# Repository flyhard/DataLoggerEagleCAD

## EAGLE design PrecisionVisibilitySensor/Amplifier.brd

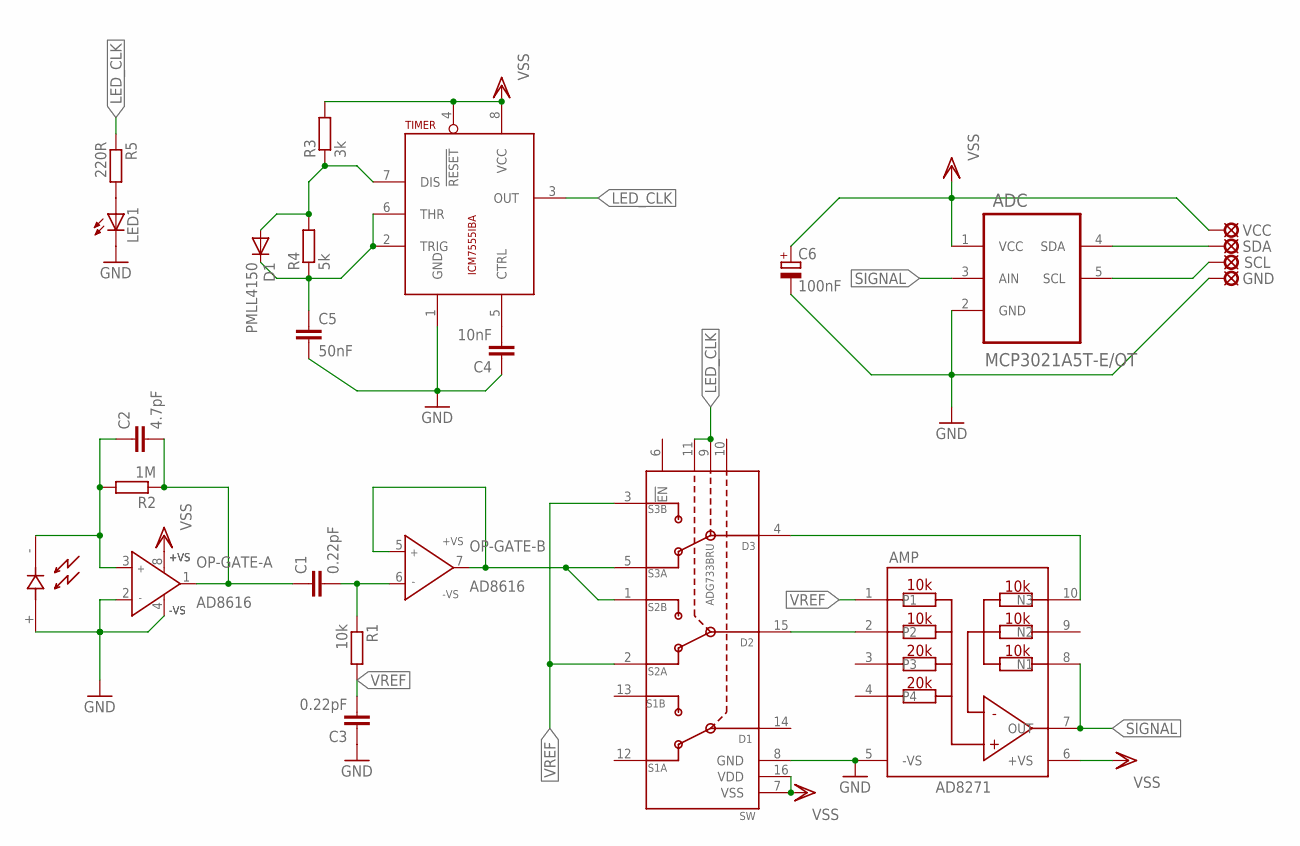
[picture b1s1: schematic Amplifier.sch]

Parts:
ADC: MCP3021A5T-E/OT; SOT95P270X145-5N
AMP: AD8271; MSOP10
C1, C3: 0.22pF; C1206
C2: 4.7pF; C1206
C4: 10nF; C1206
C5: 50nF; C1206
C6: 100nF; SMC_B
D1: PMLL4150; SOD80C
GND: LSP10
LED1: LED5MM
OP-: AD8616; MSOP08
R1: 10k; R1206
R2: 1M; R1206
R3: 3k; R1206
R4: 5k; R1206
R5: 220R; R1206
SCL: LSP10
SDA: LSP10
SW: ADG733BRU; TSSOP16
TIMER: ICM7555IBA; SOIC8
U$1: VBT101BH; TO-46
VCC: LSP10

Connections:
GND: ADC.2 (GND), AMP.5 (-VS), C3.1, C4.1, C5.2, C6.-, GND.MP, LED1.K (C), OP-.2 (IN-), OP-.4 (-VS), SW.8 (GND), TIMER.1 (GND), U$1.+
LED_CLK: SW.9 (A2), SW.11 (A0), TIMER.3 (OUT)
unnamed: OP-.5 (IN+), OP-.7 (OUT), SW.1 (S2B), SW.5 (S3A)
unnamed: AMP.10 (N3), SW.4 (D3)
unnamed: AMP.2, SW.15 (D2)
unnamed: ADC.5 (SCL), SCL.MP
unnamed: C1.2, OP-.6 (IN-), R1.1
unnamed: C1.1, C2.2, OP-.1 (OUT), R2.1
unnamed: C2.1, OP-.3 (IN+), R2.2, U$1.-
unnamed: LED1.A, R5.2
unnamed: C5.1, D1.C, R4.1, TIMER.2 (TRIG), TIMER.6 (THR)
unnamed: D1.A, R3.1, R4.2, TIMER.7 (DIS)
unnamed: ADC.4 (SDA), SDA.MP
unnamed: C4.2, TIMER.5 (CTRL)
SIGNAL: ADC.3 (AIN), AMP.7 (OUT), AMP.8 (N1)
VREF: AMP.1, C3.2, R1.2, SW.2 (S2A), SW.3 (S3B)
VSS: ADC.1 (VCC), AMP.6 (+VS), C6.+, OP-.8 (+VS), R3.2, SW.7 (VSS), SW.16 (VDD), TIMER.4 (!RESET), TIMER.8 (VCC), VCC.MP

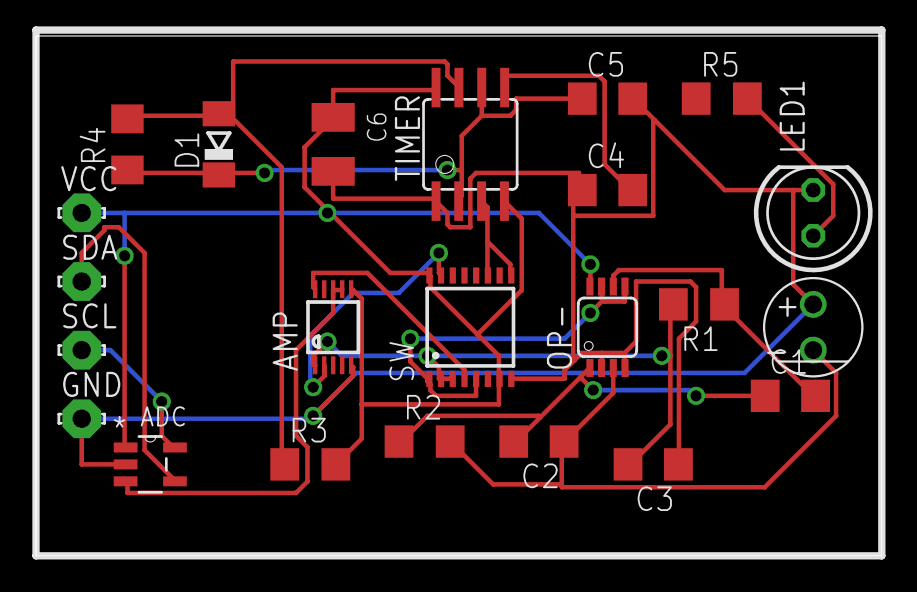
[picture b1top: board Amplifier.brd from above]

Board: 2 copper layers, 47.0 x 28.9 mm, 23 parts (0 on the bottom side), 17 nets.

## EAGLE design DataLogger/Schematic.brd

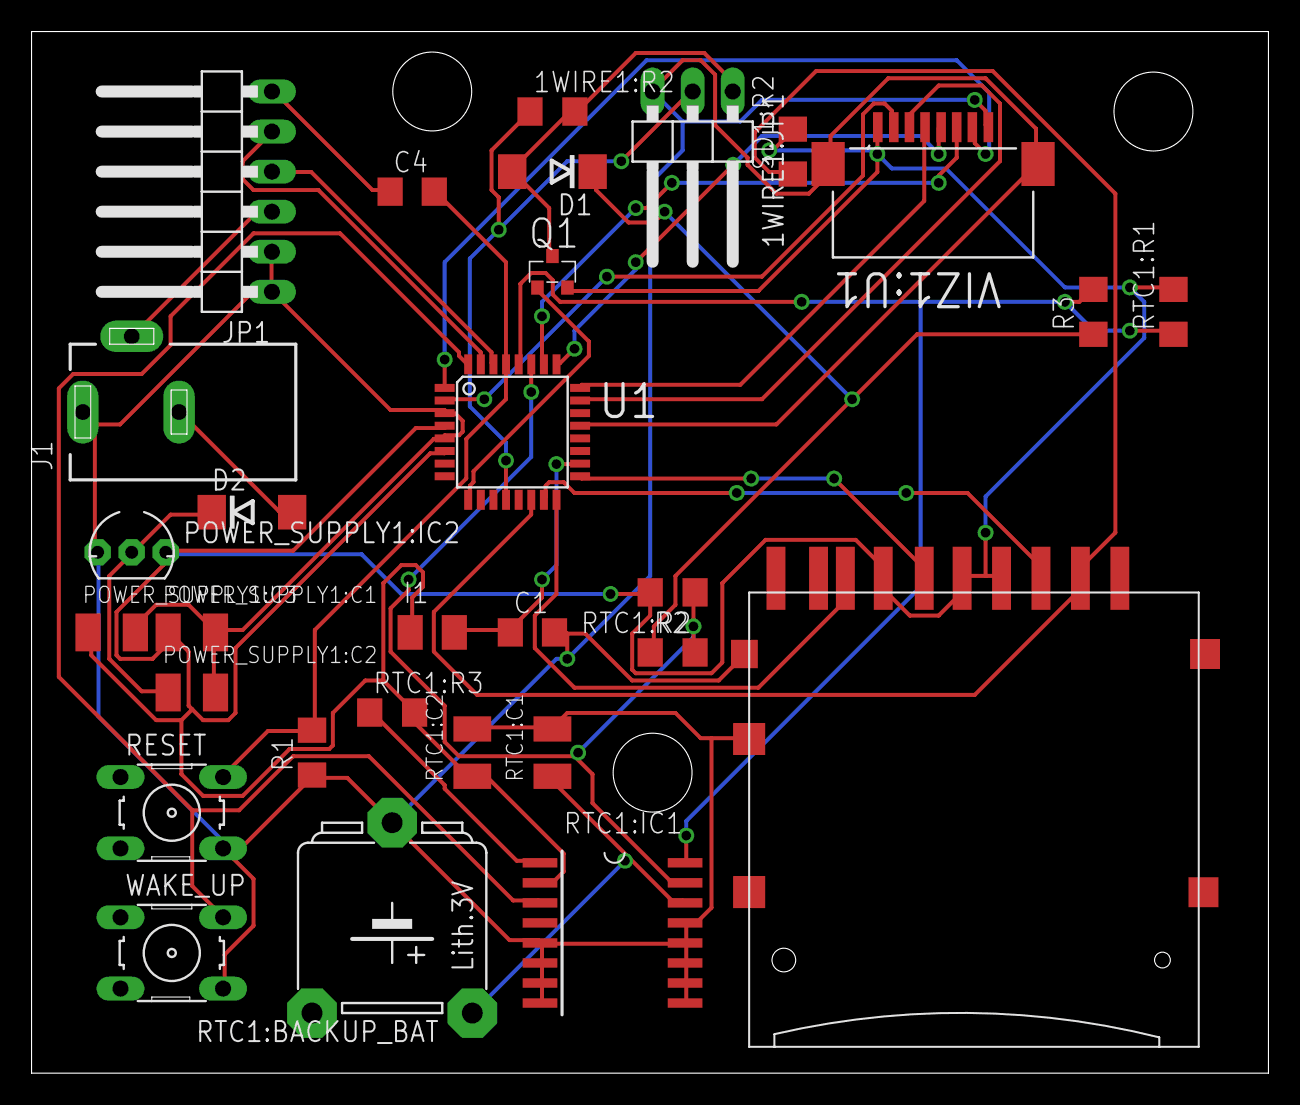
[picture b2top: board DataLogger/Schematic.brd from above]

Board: 2 copper layers, 78.4 x 66.0 mm, 30 parts (0 on the bottom side), 29 nets.

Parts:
1WIRE1:JP1: 1X03/90
1WIRE1:R2: 4,7k; R1206
C1, C4: 100nF; C1206
D1, D2: DO214AA
I1: 10nH; L3225M
J1: DCJ0202
JP1: FTDI friend; 1X06/90
POWER_SUPPLY1:C1: 0.33nF; SMC_B
POWER_SUPPLY1:C2, POWER_SUPPLY1:C3: 100nF; SMC_B
POWER_SUPPLY1:IC2: MCP1700 3302E; TO92-INLINE
Q1: IRLML5203; MICRO3
R1: 1M; R1206
R2, R3: 10k; R1206
RESET: B3F-10XX
RTC1:BACKUP_BAT: CR03N
RTC1:C1, RTC1:C2: 0.1F; SMC_B
RTC1:IC1: DS3231SN; SOIC-16W
RTC1:R1, RTC1:R2, RTC1:R3: 10k; R1206
SD1:R2: 10k; R1206
SD1:U$1: SDMMC18650; SDCARD
U1: ATMEGA328P-AU; TQFP32-08
VIZ1:U1: 52207-0885; MOLEX_52207-0885
WAKE_UP: B3F-10XX

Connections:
A0: U1.23, VIZ1:U1.3
A1: U1.24, VIZ1:U1.4
A2: U1.25, VIZ1:U1.5
A3: U1.26, VIZ1:U1.6
A4: R2.2, RTC1:IC1.15, RTC1:R2.1, U1.27
A5: R3.2, RTC1:IC1.16, RTC1:R1.1, U1.28
AVCC: C1.1, I1.2, U1.18
D2: RTC1:IC1.3, U1.32, WAKE_UP.2
D3: U1.1, VIZ1:U1.7
D4: U1.2, VIZ1:U1.2
D5: Q1.1, U1.9
D8: 1WIRE1:JP1.2, 1WIRE1:R2.1, U1.12
D10: SD1:R2.1, SD1:U$1.1, U1.14
D11: SD1:U$1.2, U1.15
D12: SD1:U$1.7, U1.16
D13: SD1:U$1.5, U1.17
DTR: C4.1, JP1.6
GND: 1WIRE1:JP1.3, C1.2, J1.1, JP1.1, JP1.2, POWER_SUPPLY1:C1.-, POWER_SUPPLY1:C2.-, POWER_SUPPLY1:C3.-, POWER_SUPPLY1:IC2.1, R1.1, RESET.4, RTC1:BACKUP_BAT.-, RTC1:C1.-, RTC1:C2.-, RTC1:IC1.5, RTC1:IC1.6, RTC1:IC1.7, RTC1:IC1.8, RTC1:IC1.9, RTC1:IC1.10, RTC1:IC1.11, RTC1:IC1.12, RTC1:IC1.13, SD1:U$1.COM, SD1:U$1.MT1, U1.3, U1.5, U1.21, VIZ1:U1.8, VIZ1:U1.9, VIZ1:U1.10, WAKE_UP.4
unnamed: D2.A, J1.3
unnamed: D2.C, POWER_SUPPLY1:C2.+, POWER_SUPPLY1:IC2.2
unnamed: D1.C, R2.1, R3.1
RESET: C4.2, R1.2, RESET.2, U1.29
RTC1:32KHZ: RTC1:IC1.1, RTC1:R3.1
RTC1:VBAT: RTC1:BACKUP_BAT.+, RTC1:C1.+, RTC1:IC1.14
RX: JP1.5, U1.31
TX: JP1.4, U1.30
VCC: I1.1, POWER_SUPPLY1:C1.+, POWER_SUPPLY1:C3.+, POWER_SUPPLY1:IC2.3, Q1.2, RTC1:C2.+, RTC1:IC1.2, RTC1:R1.2, RTC1:R2.2, RTC1:R3.2, SD1:R2.2, SD1:U$1.3, SD1:U$1.4, SD1:U$1.6, U1.4, U1.6, VIZ1:U1.1
VCC5V: J1.2, JP1.3
VSS_SWITCHED: 1WIRE1:JP1.1, 1WIRE1:R2.2, D1.A, Q1.3

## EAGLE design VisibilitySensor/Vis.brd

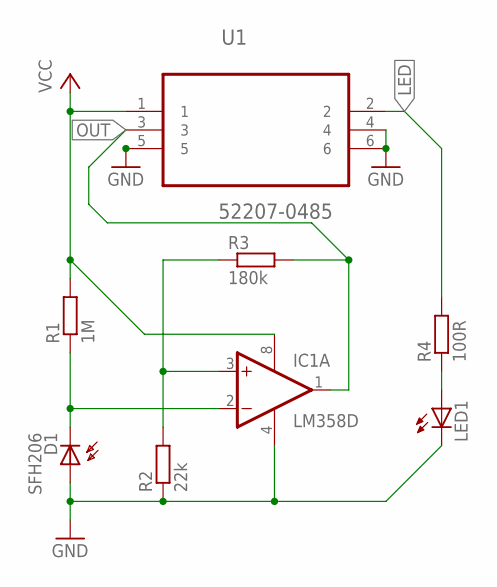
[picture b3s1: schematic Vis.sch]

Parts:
D1: SFH206
IC1: LM358D; SO08; MPN LM358DR
LED1: LED5MM; MPN 151053GS03000
R1: 1M; R1206
R2: 22k; R1206
R3: 180k; R1206; MPN CRGH1206F180K
R4: 100R; R1206
U1: 52207-0485; MOLEX_52207-0485

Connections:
GND: D1.A, IC1.4 (V-), LED1.K (C), R2.1, U1.4, U1.5, U1.6
LED: R4.2, U1.2
unnamed: D1.K (C), IC1.2 (-IN), R1.1
unnamed: LED1.A, R4.1
unnamed: IC1.3 (+IN), R2.2, R3.1
OUT: IC1.1 (OUT), R3.2, U1.3
VCC: IC1.8 (V+), R1.2, U1.1

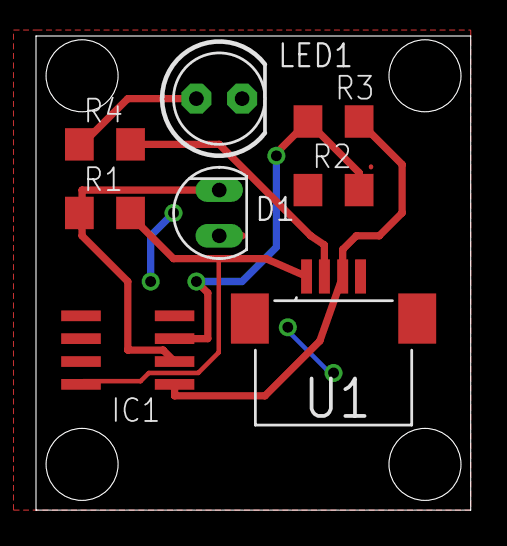
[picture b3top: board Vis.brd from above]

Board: 2 copper layers, 24.2 x 26.3 mm, 8 parts (0 on the bottom side), 7 nets.

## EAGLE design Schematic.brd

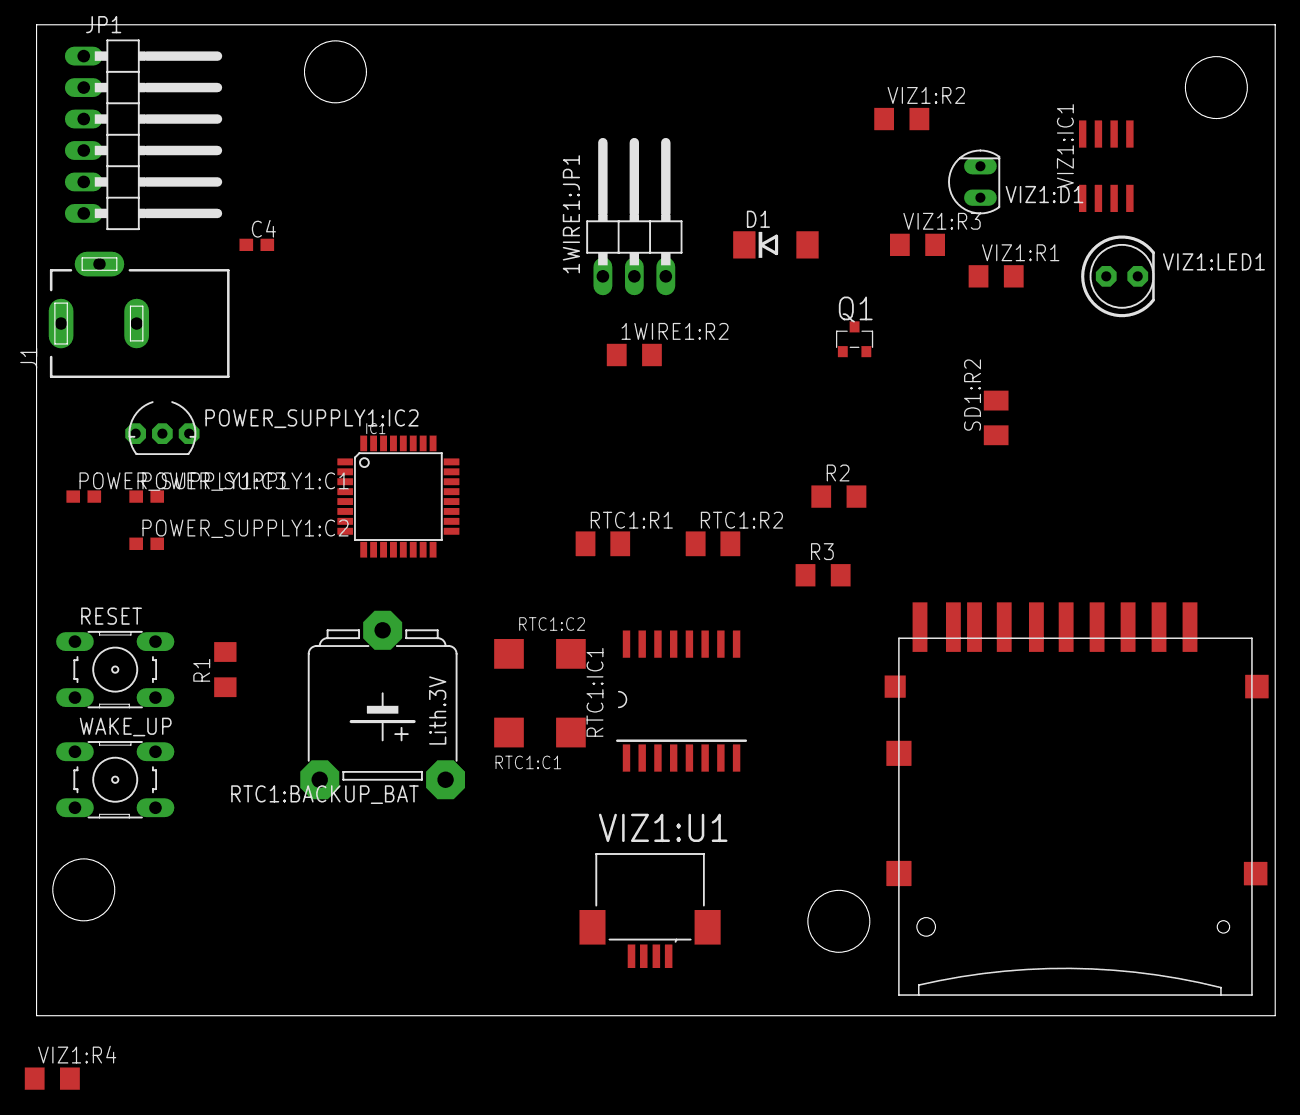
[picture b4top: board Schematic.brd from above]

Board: 2 copper layers, 100.0 x 80.0 mm, 33 parts (0 on the bottom side), 25 nets, no tracks yet.

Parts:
1WIRE1:JP1: 1X03/90
1WIRE1:R2: 4,7k; R1206
C4: 100nF; C1608
D1: DO214AA
IC1: MEGA8-AI; TQFP32-08
J1: DCJ0202
JP1: FTDI friend; 1X06/90
POWER_SUPPLY1:C1: 0.33nF; C1608
POWER_SUPPLY1:C2, POWER_SUPPLY1:C3: 100nF; C1608
POWER_SUPPLY1:IC2: MCP1700 3302E; TO92-INLINE
Q1: IRLML5203; MICRO3
R1: 1M; R1206
R2, R3: 10k; R1206
RESET: B3F-10XX
RTC1:BACKUP_BAT: CR03N
RTC1:C1, RTC1:C2: SMC_C
RTC1:IC1: SOIC-16W
RTC1:R1, RTC1:R2: M1206
SD1:R2: 10k; M1206
SD1:U$1: SDMMC18650; SDCARD
VIZ1:D1: SFH206
VIZ1:IC1: LM358D; SO08
VIZ1:LED1: LED5MM
VIZ1:R1: 1M; R1206
VIZ1:R2: 22k; R1206
VIZ1:R3: 180k; R1206
VIZ1:R4: R1206
VIZ1:U1: 52207-0485; MOLEX_52207-0485
WAKE_UP: B3F-10XX

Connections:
DTR: C4.1, JP1.6
GND: 1WIRE1:JP1.3, IC1.3, IC1.5, J1.1, JP1.1, JP1.2, R1.1, RESET.4, RTC1:BACKUP_BAT.-, RTC1:C1.-, RTC1:C2.-, RTC1:IC1.5, RTC1:IC1.6, RTC1:IC1.7, RTC1:IC1.8, RTC1:IC1.9, RTC1:IC1.10, RTC1:IC1.11, RTC1:IC1.12, RTC1:IC1.13, SD1:U$1.COM, SD1:U$1.MT1, VIZ1:D1.A, VIZ1:IC1.4, VIZ1:LED1.K, VIZ1:R2.1, VIZ1:U1.4, VIZ1:U1.5, VIZ1:U1.6, WAKE_UP.4
unnamed: IC1.9, Q1.1
unnamed: J1.3, POWER_SUPPLY1:C2.1, POWER_SUPPLY1:IC2.2
unnamed: POWER_SUPPLY1:C1.2, POWER_SUPPLY1:C2.2, POWER_SUPPLY1:C3.2, POWER_SUPPLY1:IC2.1
unnamed: IC1.28, R3.2, RTC1:R1.2
unnamed: IC1.27, R2.2, RTC1:R2.2
unnamed: IC1.15, SD1:U$1.2
unnamed: IC1.14, SD1:R2.1, SD1:U$1.1
unnamed: IC1.32, RTC1:IC1.3, WAKE_UP.2
unnamed: 1WIRE1:JP1.2, 1WIRE1:R2.1, IC1.12
unnamed: D1.C, R2.1, R3.1
unnamed: IC1.23, VIZ1:R4.2, VIZ1:U1.2
unnamed: IC1.24, VIZ1:IC1.1, VIZ1:R3.2
RESET: C4.2, IC1.29, R1.2, RESET.2
RTC1:N$1: RTC1:IC1.15, RTC1:R2.1
RTC1:N$2: RTC1:IC1.16, RTC1:R1.1
RTC1:VBAT: RTC1:BACKUP_BAT.+, RTC1:C1.+, RTC1:IC1.14
RX: IC1.31, JP1.5
VCC: POWER_SUPPLY1:C1.1, POWER_SUPPLY1:C3.1, POWER_SUPPLY1:IC2.3, Q1.2, RTC1:C2.+, RTC1:IC1.2, SD1:R2.2, SD1:U$1.3, SD1:U$1.6, VIZ1:IC1.8, VIZ1:R1.2
VCC5V: J1.2, JP1.3
VIZ1:N$1: VIZ1:D1.K, VIZ1:IC1.2, VIZ1:R1.1
VIZ1:N$2: VIZ1:LED1.A, VIZ1:R4.1
VIZ1:N$3: VIZ1:IC1.3, VIZ1:R2.2, VIZ1:R3.1
VSS_SWITCHED: 1WIRE1:JP1.1, 1WIRE1:R2.2, D1.A, Q1.3

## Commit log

2015-08-12 Added
2015-08-12 More components
2015-08-12 More development
2015-08-12 More libs
2015-08-13 Slight changes
2015-08-13 Moved stuff around
2015-08-13 Added sample visibility sensor
2015-08-13 Updated layout
2015-08-13 Rerouted stuff and replaced with better parts.
2015-08-14 Improvements
2015-08-17 Added amplifier
2015-08-25 Ignored all png-s
2015-08-26 Lots of updates
2015-08-27 Renamed Project
2017-09-11 Added exported schematics
2017-09-11 added partlist
2017-09-11 Added Fritzing version of the schematic and a port layout of the AtMega chip
2017-09-11 Mostly done
2017-09-12 Finally got the traces right
2017-09-13 More fine tuning
